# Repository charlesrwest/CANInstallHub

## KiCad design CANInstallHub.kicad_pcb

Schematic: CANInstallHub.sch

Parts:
C1, C2: GRM188R61A106KE69D
C3, C6, C7, C10: GRM155R71C104KA88D
C4: C1005X5R1A105K050BB
C5: VJ0402Y103KXJCW1BC
C8, C9: 0402ZD475MAT2A
C11: UBC1E221MNS1GS
C12, C13: GRM1555C1H300FA01J
D1: 720-LYQ396P1Q236
J4H-CAN1, J4H-CAN2, J4H-CAN3, J4H-CAN4, J4H-CAN5, J4H-CAN6, J4H-CAN7, J4H-CAN8, J4H-CAN9, J4H-CAN10: 4PINHEADER-CAN
J4H-I2C1, J4H-I2C2, J4H-I2C3, J4H-I2C4, J4H-I2C5, J4H-I2C6, J4H-I2C7, J4H-I2C8, J4H-I2C9, J4H-I2C10: 4PINHEADER-I2C
J6H1: 6PINHEADER
J10H-GPIO1: 10PINHEADER-GPIO
MCU1: STM32F072C8T6
Q1, Q2: DMP3099L-7
R1: RR0510P-101-D
R2: RR0510P-103-D
R3: RR0510P-121-D
R4, R5: RR0510P-102-D
SW1, SW2: PTS810 SJM 250 SMTR LFS
TFJ1: TJF1051T/3
U1: NCP1117ST33T3G
USB1: 10104111-0001LF
X1: ABLS-8.000MHZ-B4-T

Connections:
+3.3V: C2.1, C3.2, C4.1, C5.1, C7.2, C8.2, C9.1, C10.1, C11.1, J4H-CAN1.1, J4H-CAN2.1, J4H-CAN3.1, J4H-CAN4.1, J4H-CAN5.1, J4H-CAN6.1, J4H-CAN7.1, J4H-CAN8.1, J4H-CAN9.1, J4H-CAN10.1, J4H-I2C1.1, J4H-I2C2.1, J4H-I2C3.1, J4H-I2C4.1, J4H-I2C5.1, J4H-I2C6.1, J4H-I2C7.1, J4H-I2C8.1, J4H-I2C9.1, J4H-I2C10.1, MCU1.1 (VBAT), MCU1.9 (VDDA), MCU1.24 (VDD), MCU1.36 (VDDIO2), MCU1.48 (VDD), R2.2, R4.2, R5.2, SW2.2, TFJ1.8 (VIO), U1.2 (VO)
+5V: C1.1, Q1.S, Q2.S, TFJ1.3 (VCC), U1.3 (VI)
GND: C1.2, C2.2, C3.1, C4.2, C5.2, C6.2, C7.1, C8.1, C9.2, C10.2, C11.2, C12.1, C13.1, D1.2 (K), J4H-CAN1.4, J4H-CAN2.4, J4H-CAN3.4, J4H-CAN4.4, J4H-CAN5.4, J4H-CAN6.4, J4H-CAN7.4, J4H-CAN8.4, J4H-CAN9.4, J4H-CAN10.4, J4H-I2C1.4, J4H-I2C2.4, J4H-I2C3.4, J4H-I2C4.4, J4H-I2C5.4, J4H-I2C6.4, J4H-I2C7.4, J4H-I2C8.4, J4H-I2C9.4, J4H-I2C10.4, J6H1.6 (GND), MCU1.8 (VSSA), MCU1.23 (VSS), MCU1.35 (VSS), MCU1.47 (VSS), Q1.G, Q2.G, SW1.2, TFJ1.2 (GND), U1.1 (GND), USB1.5 (GND)
unnamed: C6.1, MCU1.7 (NRST), SW1.1
unnamed: MCU1.44 (BOOT0), SW2.1
unnamed: J6H1.1 (VCC), Q1.D
unnamed: Q2.D, USB1.1 (5V)
unnamed: J6H1.4 (RTS), MCU1.11 (PA1)
unnamed: MCU1.32 (PA11), USB1.2 (D-)
unnamed: MCU1.33 (PA12), USB1.3 (D+)
unnamed: J6H1.5 (CTS), MCU1.10 (PA0)
unnamed: J6H1.3 (Tx), MCU1.12 (PA2)
unnamed: J6H1.2 (Rx), MCU1.13 (PA3)
unnamed: C13.2, MCU1.5 (PF0-OSC_IN), X1.2
unnamed: C12.2, MCU1.6 (PF1-OSC_OUT), X1.1
unnamed: MCU1.37 (PA14), R1.1
unnamed: D1.1 (A), R1.2
unnamed: J10H-GPIO1.8, MCU1.21 (PB10)
unnamed: J10H-GPIO1.9, MCU1.22 (PB11)
unnamed: J10H-GPIO1.1, MCU1.14 (PA4)
unnamed: J10H-GPIO1.2, MCU1.15 (PA5)
unnamed: J10H-GPIO1.3, MCU1.16 (PA6)
unnamed: J10H-GPIO1.4, MCU1.17 (PA7)
unnamed: J10H-GPIO1.5, MCU1.18 (PB0)
unnamed: J10H-GPIO1.6, MCU1.19 (PB1)
unnamed: J10H-GPIO1.7, MCU1.20 (PB2)
unnamed: J10H-GPIO1.10, MCU1.25 (PB12)
unnamed: J4H-CAN1.2, J4H-CAN2.2, J4H-CAN3.2, J4H-CAN4.2, J4H-CAN5.2, J4H-CAN6.2, J4H-CAN7.2, J4H-CAN8.2, J4H-CAN9.2, J4H-CAN10.2, R3.1, TFJ1.6 (CANH)
unnamed: J4H-CAN1.3, J4H-CAN2.3, J4H-CAN3.3, J4H-CAN4.3, J4H-CAN5.3, J4H-CAN6.3, J4H-CAN7.3, J4H-CAN8.3, J4H-CAN9.3, J4H-CAN10.3, R3.2, TFJ1.7 (CANL)
unnamed: MCU1.45 (PB8), TFJ1.4 (RXD)
unnamed: MCU1.41 (PB5), R2.1, TFJ1.5 (S)
unnamed: MCU1.46 (PB9), TFJ1.1 (TXD)
unnamed: J4H-I2C1.3, J4H-I2C2.3, J4H-I2C3.3, J4H-I2C4.3, J4H-I2C5.3, J4H-I2C6.3, J4H-I2C7.3, J4H-I2C8.3, J4H-I2C9.3, J4H-I2C10.3, MCU1.43 (PB7), R5.1
unnamed: J4H-I2C1.2, J4H-I2C2.2, J4H-I2C3.2, J4H-I2C4.2, J4H-I2C5.2, J4H-I2C6.2, J4H-I2C7.2, J4H-I2C8.2, J4H-I2C9.2, J4H-I2C10.2, MCU1.42 (PB6), R4.1

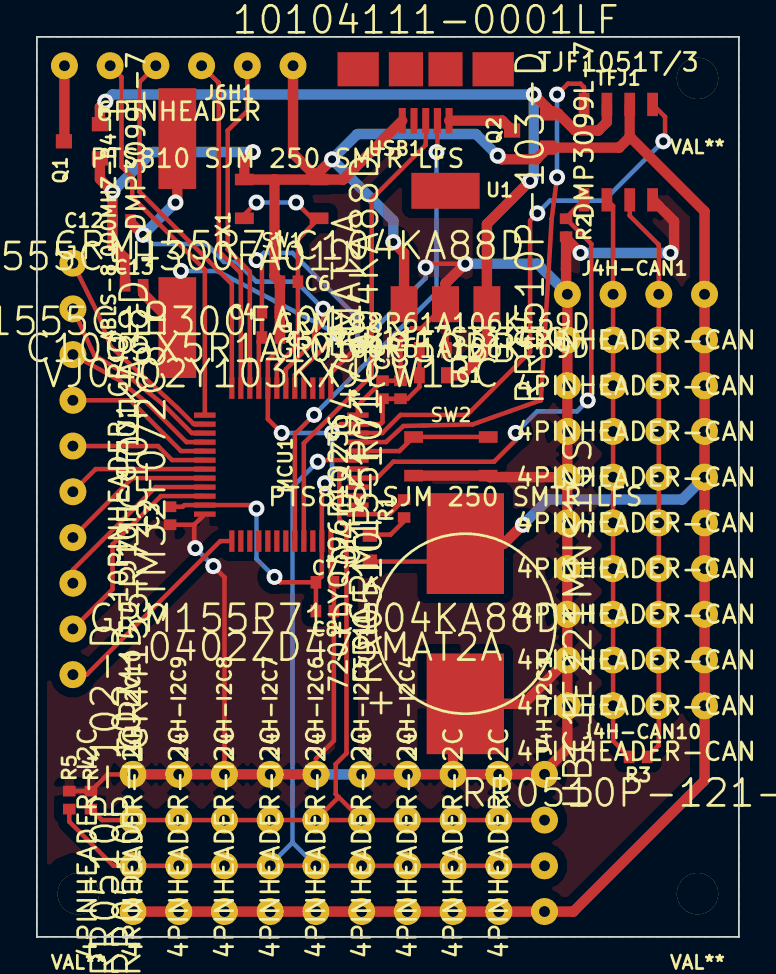
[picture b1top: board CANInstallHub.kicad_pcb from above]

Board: 2 copper layers, 39.0 x 50.0 mm, 53 parts (0 on the bottom side), 34 nets.

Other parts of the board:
M2MountingHole, M2MountingHole#2, M2MountingHole#3: VAL**; M2MountingHole

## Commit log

2015-10-04 Complete files for version 0.
2015-10-06 Version 0.1.
2015-10-21 Lastest revision.
